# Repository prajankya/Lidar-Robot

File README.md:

## Unmanned Mapping Vehicle Using L.O.A.M. in Real-time
 L.O.A.M. - Lidar Odometry and Mapping in Real-time

This project is about an Unmanned Mobile Robot using L.O.A.M. (Lidar, Odometry And Mapping) in Real-time.

## Abstract
The robot uses a Laser distance sensor(Lidar) which gives distance to the first obstacle in its line-of-sight and the sensor. Making this sensor rotate gives us distance of all the obstacles from the sensor, which in fact is the map of the surrounding. This sensor, with other sensors like odometry and IMU(Inertial measurement Unit), mounted on a mobile moving base and complex algorithms driving the robot autonomously help make a to-scale map of the surrounding.

## Basic contruction
The Bot uses ROS(Robot Operating System) at its core running on a compact mobile CPU. It uses IMU(Inertial measurement Unit) for its orientation feedback. The base comprise of a square frame with four omni wheel on its corners driven by high torque BLDC motors. The Bot works on 24v DC and have internal power distribution and conversion unit. The bot first takes in the lidar input, and process that into a map fusing together with  odometry input and IMU input. The Odometry sensor is a “Castor Feedback sensor” which consist of two rotary encoders, one reading the angle or rotation, and other the length in that direction. This type of feedback can be universally used for any type of terrain robots with very good accuracy. This bot can be controlled from a remote computer, on which we can even see the 3D Model and see the model within the map in Real time. The GUI remote can be used to save the map or load the map in the system. Taking all the properties in consideration,  Lidar Robot with L.O.A.M. is a very robust platform with variety of robotics applications.

## How to Install
rosdep install --from-paths /opt/ros/jade --ignore-src

rosdep install --from-paths Lidar-Robot/src --ignore-src

6th sem, 2017 Batch  
Department of Automation and Robotics.  
B. V. Bhoomaraddi College of Engineering and Technology, Hubli

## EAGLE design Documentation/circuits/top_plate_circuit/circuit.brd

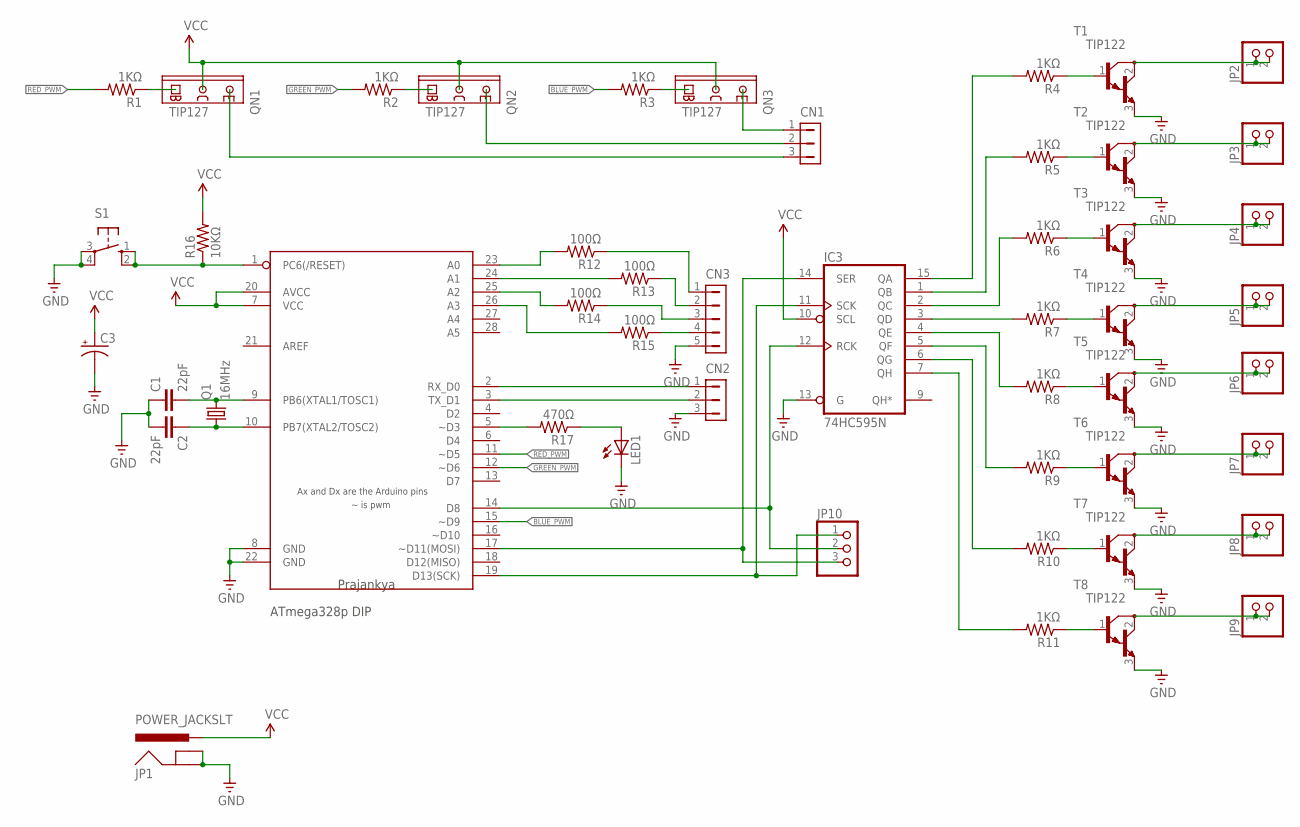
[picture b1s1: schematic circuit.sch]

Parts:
C1, C2: 22pF; C025-025X050
C3: CPOL-USTT2D6L; TT2D6L
CN1, CN2: HDR-1X3-70543-?; 70543-03
CN3: HDR-1X5-70543-?; 70543-05
IC3: 74HC595N; DIL16
JP1: POWER_JACKSLT; POWER_JACK_SLOT
JP2, JP3, JP4, JP5, JP6, JP7, JP8, JP9: PINHD-1X2; 1X02
JP10: PINHD-1X3; 1X03
LED1: LED5MM
Q1: 16MHz; HC49U-V
QN1, QN2, QN3: TIP127; TO220AV
R1, R2, R3, R4, R5, R6, R7, R8, R9, R10, R11: 1KΩ; AXIAL-0.4
R12, R13, R14, R15: 100Ω; AXIAL-0.4
R16: 10KΩ; 0207/10
R17: 470Ω; 0207/12
S1: 10-XX; B3F-10XX
T1, T2, T3, T4, T5, T6, T7, T8: TIP122; TO220
U$1: ATMEGA328P_DIP; ATMEGA328_CUSTOMPAD

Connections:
BLUE_PWM: R3.P$2 (2), U$1.15 (~D9)
GND: C1.1, C2.2, C3.-, CN2.3, CN3.5, IC3.8 (GND), IC3.13 (G), JP1.GND@1 (GNDBREAK), JP1.GND@2 (GND), LED1.K (C), S1.3, S1.4 (P1), T1.3 (E), T2.3 (E), T3.3 (E), T4.3 (E), T5.3 (E), T6.3 (E), T7.3 (E), T8.3 (E), U$1.8 (GND), U$1.22 (GND)
GREEN_PWM: R2.P$2 (2), U$1.12 (~D6)
N1: JP2.1, JP2.2, T1.2 (C)
N2: JP3.1, JP3.2, T2.2 (C)
N3: JP4.1, JP4.2, T3.2 (C)
N4: JP5.1, JP5.2, T4.2 (C)
N5: JP6.1, JP6.2, T5.2 (C)
N6: JP7.1, JP7.2, T6.2 (C)
N7: JP8.1, JP8.2, T7.2 (C)
N8: JP9.1, JP9.2, T8.2 (C)
unnamed: CN1.3, QN1.E
unnamed: CN1.2, QN2.E
unnamed: CN1.1, QN3.E
unnamed: QN1.B, R1.P$1 (1)
unnamed: QN2.B, R2.P$1 (1)
unnamed: QN3.B, R3.P$1 (1)
unnamed: R4.P$1 (1), T1.1 (B)
unnamed: R5.P$1 (1), T2.1 (B)
unnamed: R12.P$2 (2), U$1.23 (A0)
unnamed: IC3.15 (QA), R4.P$2 (2)
unnamed: R13.P$2 (2), U$1.24 (A1)
unnamed: IC3.1 (QB), R5.P$2 (2)
unnamed: R6.P$1 (1), T3.1 (B)
unnamed: R14.P$2 (2), U$1.25 (A2)
unnamed: IC3.2 (QC), R6.P$2 (2)
unnamed: R7.P$1 (1), T4.1 (B)
unnamed: R15.P$2 (2), U$1.26 (A3)
unnamed: IC3.3 (QD), R7.P$2 (2)
unnamed: R8.P$1 (1), T5.1 (B)
unnamed: CN2.1, U$1.2 (RX_D0)
unnamed: IC3.4 (QE), R8.P$2 (2)
unnamed: R9.P$1 (1), T6.1 (B)
unnamed: CN2.2, U$1.3 (TX_D1)
unnamed: IC3.5 (QF), R9.P$2 (2)
unnamed: R10.P$1 (1), T7.1 (B)
unnamed: R17.2, U$1.5 (~D3)
unnamed: IC3.6 (QG), R10.P$2 (2)
unnamed: R11.P$1 (1), T8.1 (B)
unnamed: LED1.A, R17.1
unnamed: IC3.7 (QH), R11.P$2 (2)
unnamed: IC3.11 (SCK), JP10.1, U$1.19 (D13(SCK))
unnamed: IC3.12 (RCK), JP10.2, U$1.14 (D8)
unnamed: C2.1, Q1.1, U$1.10 (PB7(XTAL2/TOSC2))
unnamed: C1.2, Q1.2, U$1.9 (PB6(XTAL1/TOSC1))
unnamed: CN3.1, R12.P$1 (1)
unnamed: CN3.2, R13.P$1 (1)
unnamed: CN3.3, R14.P$1 (1)
unnamed: CN3.4, R15.P$1 (1)
unnamed: IC3.14 (SER), JP10.3, U$1.17 (~D11(MOSI))
unnamed: R16.1, S1.1 (S), S1.2 (S1), U$1.1 (PC6(/RESET))
RED_PWM: R1.P$2 (2), U$1.11 (~D5)
VCC: C3.+, IC3.10 (SCL), IC3.16 (VCC), JP1.PWR, QN1.C, QN2.C, QN3.C, R16.2, U$1.7 (VCC), U$1.20 (AVCC)

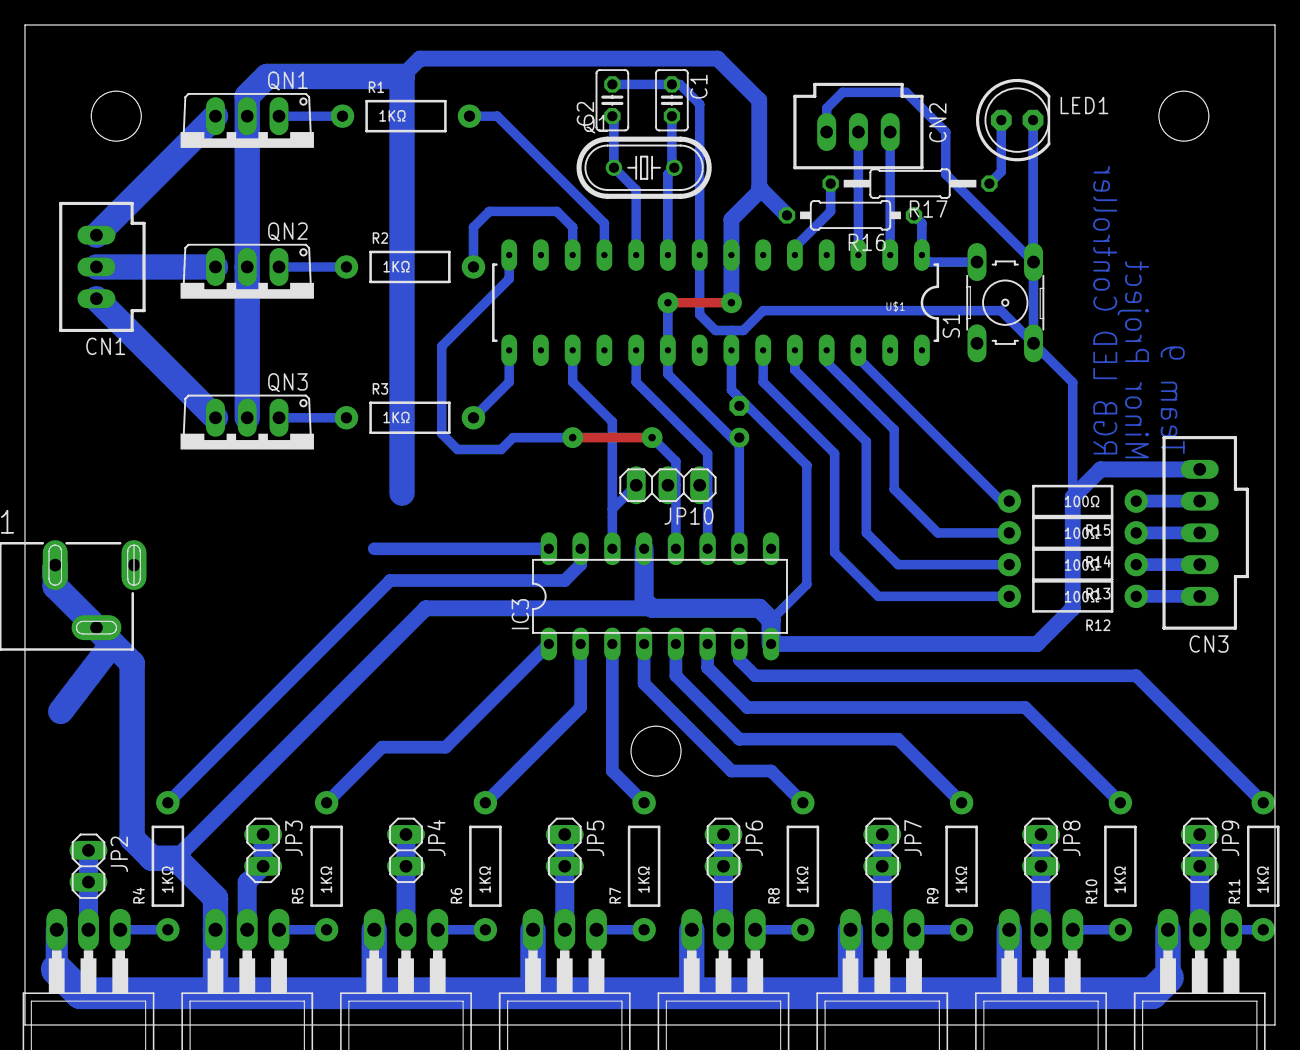
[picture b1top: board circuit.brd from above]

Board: 2 copper layers, 100.0 x 80.0 mm, 49 parts (1 on the bottom side), 53 nets.

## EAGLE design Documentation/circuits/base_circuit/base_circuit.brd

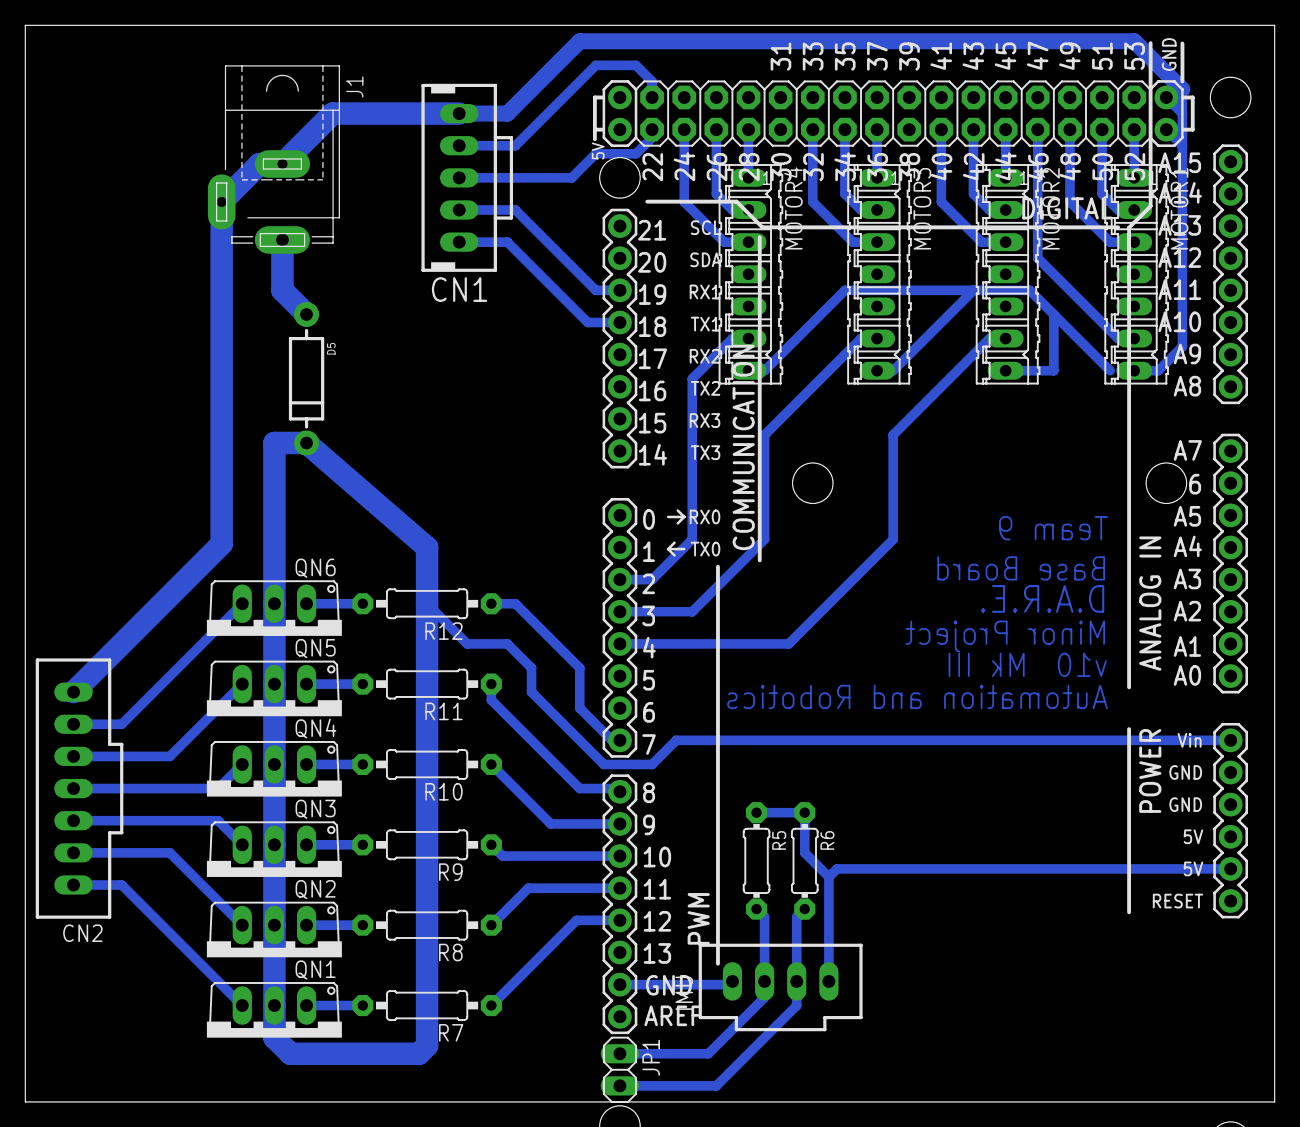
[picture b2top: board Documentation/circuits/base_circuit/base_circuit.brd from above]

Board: 2 copper layers, 98.7 x 85.1 mm, 25 parts (0 on the bottom side), 44 nets.

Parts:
CN1: MTE-100-5VL
CN2: 70543-07
D5: DIODE-1N4001
IMU: 70543-04
J1: SPC4078
JP1: 1X02
MOTOR1: m1; 07P
MOTOR2: m2; 07P
MOTOR3: m3; 07P
MOTOR4: m4; 07P
QN1, QN2, QN3, QN4, QN5, QN6: TIP127; TO220AV
R5, R6: 2.2k; 0204/7
R7, R8, R9, R10, R11, R12: 0207/10
U1: ARDUINO-MEGAFULL; ARDUINO_MEGA

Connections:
BRAKE-M1: MOTOR1.1, U1.52
BRAKE-M2: MOTOR2.1, U1.44
BRAKE-M3: MOTOR3.1, U1.36
BRAKE-M4: MOTOR4.1, U1.28
DIR-M1: MOTOR1.3, U1.48
DIR-M2: MOTOR2.3, U1.40
DIR-M3: MOTOR3.3, U1.32
DIR-M4: MOTOR4.3, U1.24
DIS-M1: MOTOR1.2, U1.50
DIS-M2: MOTOR2.2, U1.42
DIS-M3: MOTOR3.2, U1.34
DIS-M4: MOTOR4.2, U1.26
FEEDBACK_IN1: CN1.3, U1.22
FEEDBACK_IN2: CN1.4, U1.23
FEEDBACK_INT1: CN1.1, U1.18
FEEDBACK_INT2: CN1.2, U1.19
GND: CN1.5, CN2.7, IMU.1, J1.1, J1.2, MOTOR1.7, MOTOR2.7, MOTOR3.7, MOTOR4.7, U1.GND@2, U1.GND@3, U1.GND@4
L1: R7.1, U1.12
L2: R8.1, U1.11
L3: R9.1, U1.10
L4: R10.1, U1.9
L5: R11.1, U1.8
L6: R12.1, U1.7
unnamed: QN1.B, R7.2
unnamed: QN2.B, R8.2
unnamed: QN3.B, R9.2
unnamed: QN4.B, R10.2
unnamed: QN5.B, R11.2
unnamed: QN6.B, R12.2
unnamed: D5.A, J1.3
unnamed: CN2.1, QN1.E
unnamed: CN2.2, QN2.E
unnamed: CN2.3, QN3.E
unnamed: CN2.4, QN4.E
unnamed: CN2.5, QN5.E
unnamed: CN2.6, QN6.E
SCL: IMU.3, JP1.2, R6.2
SDA: IMU.2, JP1.1, R5.2
SPEED-M1: MOTOR1.6, U1.46
SPEED-M2: MOTOR2.6, U1.4
SPEED-M3: MOTOR3.6, U1.3
SPEED-M4: MOTOR4.6, U1.2
VCC: IMU.4, R5.1, R6.1, U1.3.3V
VCC/2: D5.C, QN1.C, QN2.C, QN3.C, QN4.C, QN5.C, QN6.C, U1.VIN

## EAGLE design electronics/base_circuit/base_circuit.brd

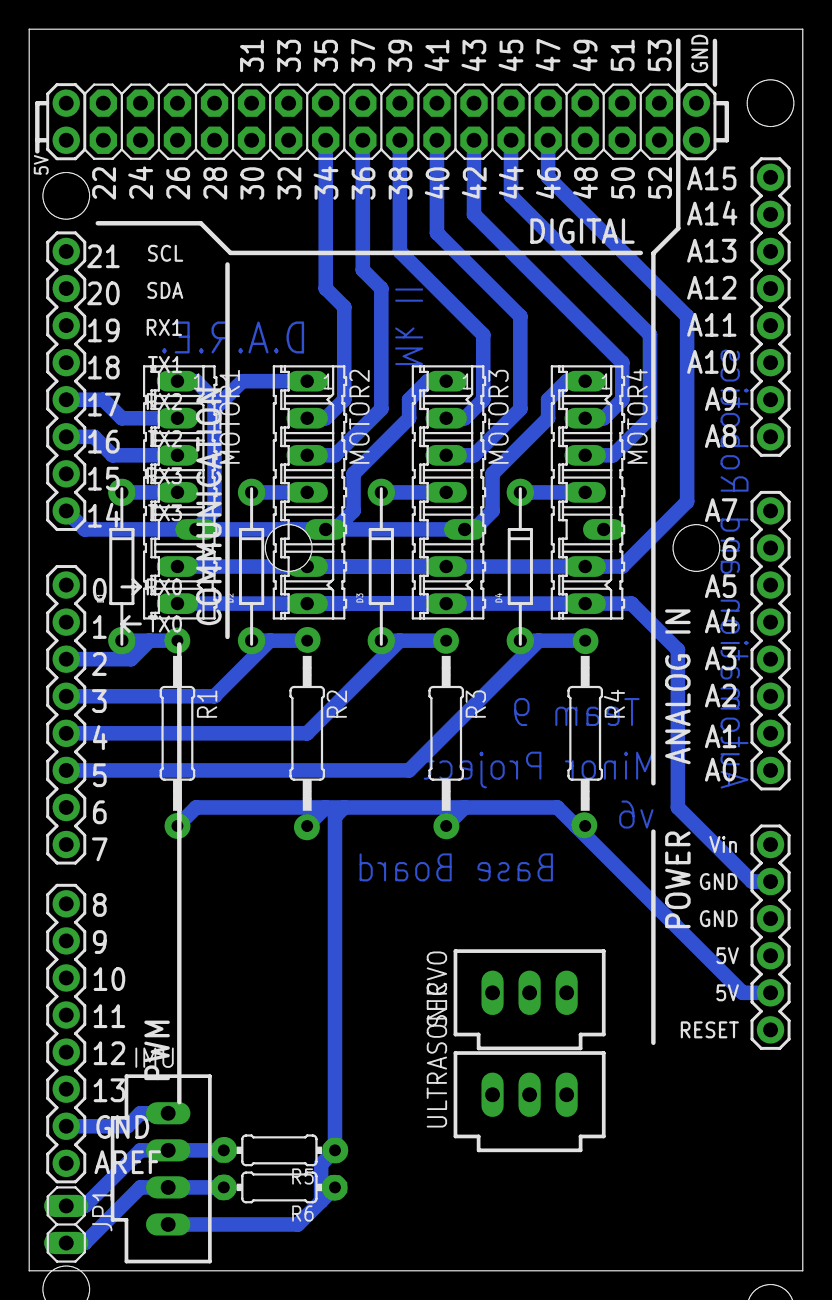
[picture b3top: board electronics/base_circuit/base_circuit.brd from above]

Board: 2 copper layers, 53.0 x 85.1 mm, 19 parts (0 on the bottom side), 23 nets.

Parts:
D1, D2, D3, D4: DIODE-1N4148
IMU: 70543-04
JP1: 1X02
MOTOR1: m1; 07P
MOTOR2: m2; 07P
MOTOR3: m3; 07P
MOTOR4: m4; 07P
R1, R2, R3, R4: 4.7k; 0207/12
R5, R6: 2.2k; 0204/7
SERVO: 70543-03
U1: ARDUINO-MEGAFULL; ARDUINO_MEGA
ULTRASONIC: 70543-03

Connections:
BRAKEPIN: MOTOR1.1, MOTOR2.1, MOTOR3.1, MOTOR4.1, U1.14
DIR-M1: MOTOR1.3, U1.16
DIR-M2: MOTOR2.3, U1.36
DIR-M3: MOTOR3.3, U1.40
DIR-M4: MOTOR4.3, U1.44
DIS-M1: MOTOR1.2, U1.17
DIS-M2: MOTOR2.2, U1.34
DIS-M3: MOTOR3.2, U1.38
DIS-M4: MOTOR4.2, U1.42
GND: IMU.1, MOTOR1.7, MOTOR2.7, MOTOR3.7, MOTOR4.7, SERVO.3, U1.GND@0, U1.GND@1, U1.GND@4
unnamed: D1.C, MOTOR1.4
unnamed: D2.C, MOTOR2.4
unnamed: D3.C, MOTOR3.4
unnamed: D4.C, MOTOR4.4
SCL: IMU.3, JP1.2, R6.2
SDA: IMU.2, JP1.1, R5.2
SPEEDPIN: MOTOR1.6, MOTOR2.6, MOTOR3.6, MOTOR4.6, U1.46
TACHO-M1: D1.A, R1.1, U1.2
TACHO-M2: D2.A, R2.1, U1.3
TACHO-M3: D3.A, R3.1, U1.4
TACHO-M4: D4.A, R4.1, U1.5
VCC: IMU.4, R1.2, R2.2, R3.2, R4.2, R5.1, R6.1, U1.3.3V
VCC/2: SERVO.2, U1.VIN

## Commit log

2016-04-02 Added Submodules
2016-04-02 Create gh-pages branch via GitHub
2016-04-02 Updateed Readme.md with author
2016-04-03 Added Datasheets in the Documentation
2016-04-03 v1 of Base circuit
2016-04-03 v1 of base program
2016-04-03 v2 of base program
2016-04-03 Initial Programs
2016-04-03 deleted electronics as it is added in the individual repo of base
2016-04-04 Removed Electronics and Programming folders as they are going in the Dedicated repositories
2016-04-04 removed download buttons
2016-04-04 solved scratch compiling closed #1
2016-04-04 updated readme with darshan link
2016-04-04 updated readme with typo @Belavatagi
2016-04-04 added link to @pujarmani
2016-04-04 Added readme
2016-04-05 Working towards #4 , added led pins
2016-04-05 Added circuits folder closed #6
2016-04-06 updated Circuit
2016-04-06 changed the whole circuit to use speed control for individula motors and also added connections for top plate design leds
2016-04-06 added master start
2016-04-08 edited BRD file
2016-04-08 Base is receiving standard message instead of custom message
2016-04-08 Edited the base program to take new speed and brake control
2016-04-09 added top plate design program functions closed #15
2016-04-09 added led functions
2016-04-09 added outIn LED function
2016-04-16 Updated Odometry output
2016-04-16 verified odom is working
2016-04-21 Added Design Service closed #16 , changed IMU use to a separate cpp, making it optional with one declare closed #19
2016-04-21 Configurable firmware
2016-04-29 Verified the problem with led design
2016-04-30 Updated URDF tf_broadcaster
2016-04-30 Adding v2 Models
2016-04-30 testing with base speed pwm problem
2016-04-30 Repaired Speed Problem, closed #24
2016-04-30 Repaired Different motor speed Problem, closed #24
2016-05-01 Repaired speed problem of motors
2016-05-02 Added magnetometer heading in between
2016-05-02 Expected working odom
2016-05-02 added Hector mapping
2016-05-27 Added Abstract to readme
2016-05-27 Added Zenodo DOI
2016-05-27 Added rendered images in CAD Models
2016-05-27 Added Documentation report and project proposal
2016-05-27 added Gui v1 design in Documentation
2016-05-27 Added Datasheet manual of RPLidar
2016-05-27 Updated Submodules to latest commits
2016-05-28 Shifted to custom website
2016-05-30 step 1 with three js
2016-06-03 Added hover
2016-06-03 added tween.js
2016-06-03 added tween.js edited original models
2016-06-05 Optimized Models with meshmixer
2016-06-05 Meshes loaded successfully, but raycaster not working individually
2016-06-14 Removed Submodules
    Updated and Unified the base code removing all the submodules
2016-06-14 Removed Gitmodules
2016-06-14 Added gitignore for devel and build folders of catkin make
2016-06-14 Added node webserver
2016-06-14 removed node modules
2016-06-14 Added node_modules in gitignore
2016-06-14 removed src
2016-06-14 Moved to src
2016-06-14 Made Server.launch file
2016-06-14 added Meshes
2016-06-14 node Server is Working
2016-06-14 Added ROS control center, Repaired the dependancy on port for index.html
2016-06-14 Added Base and tf nodes
2016-06-15 Added local javascript files, moved webserver files to a subfolder, edited server.launch added dependencies in package.xml
2016-06-15 Added Compressed files
2016-06-15 Removed control center
2016-06-15 added ROS Control Center
2016-06-15 Added how to install step in README.md
2016-06-15 Updated Solidworks Models v3
2016-06-15 Tiding the repo
2016-06-15 Moved circuits to Documentation
2016-06-15 Added STL and PLY models in CAD
2016-06-15 updates to RPlidar
2016-06-15 Moved Models in the ros package for xacro discovery
2016-06-15 Base model Down scaled
2016-06-15 further scaled down to 0.01x
2016-06-15 further scaled down to 0.001x
2016-06-15 Scaled back up the base
2016-06-15 added c clamp and shaft to the xacro
2016-06-15 Added dae of wheel and removed unrequired files
2016-06-15 setting wheel
2016-06-15 Added wheel collada with texture
2016-06-15 updating robot.xacro
2016-06-15 updating robot.xacro second wheel
2016-06-16 Updated Readme to How to install for system dependencies
2016-06-16 Added Top Plate to URDF
2016-06-16 Added circuit plate
2016-06-16 Updated server.js for spawn, printing stdout and stderr now
2016-06-16 Updated to run server seemlessly without warning of xacro
2016-06-16 Changed distance from center Changed distance from center of c clamp motor shaft and wheel to a variable
2016-06-16 Added Feedback and Studs for it
2016-06-16 Added RPlidar base in model
2016-06-16 Added RPlidar Bottom
2016-06-16 Added Lidar UP updated stud.stl with proper binary encoding
2016-06-16 Updated RVIZ
    Files working with tf jointstatepublisher and robot_tf_publisher perfectly on rviz as well as website
2016-06-16 Added keyboardteleop feature
2016-06-17 Removed host name dependency of ros-mini
2016-06-17 Cleaned a lot
2016-06-17 Added Gazebo
2016-06-17 Moved rviz to extras
2016-06-17 Updated URDF with Gazebo wheels
2016-06-17 Gazebo is functioning
2016-06-18 Added ROS-Control
    Partially added, gazebo model does not place shaft correctly yet.
2016-06-18 Added git ignore
2016-06-18 Removed Controller setup
    Removed controller as the real bot does not have any feedback on wheels, so cannot use the PID control, though gazebo provides it.
2016-06-18 Working Gazebo and rviz with movement from web UI
2016-06-18 Cleaning GH branch
2016-06-18 added three.js in javascripts
2016-06-18 Removed node modules folder
2016-06-18 Added node_modules exception in gitignore
2016-06-18 Removed optimized
2016-06-18 Made gazebo empty launch
2016-06-18 Updated meshs json with all except wheel
2016-06-18 Added motor and c clamp to model
2016-06-18 Cleaned models dir
2016-06-19 Cleaned repo, Hector SLAM not working
2016-06-19 Removed Hector slam
2016-06-19 Added connection status in web UI
2016-06-19 Move base working with 2D goal
2016-06-19 Removed Husky, unrequired folder
2016-06-20 Added Move Base, 2D Nav goals working
2016-06-27 Added frontier_exploration
2016-06-27 solving frontier git connection problem
2016-06-27 Added frontier exploration
2016-06-28 Added Auto Explorer
2016-06-28 Solved build dependancy with frontier_exploration
2016-06-28 Exploration working Cleaned repo, Auto exit node server on client close
2016-06-28 Partial commit with map on web not working so commented out
2016-06-28 Separated Core and gsim, rviz
2016-07-03 Added Create AP Package
2016-07-03 Added Create Ap to node automated the creating AP process by adding it to the default server.js
2016-07-03 Made first Page for control by mobile also added dependencies in package.xml
2016-07-03 Added Port forwarder to 80 removed all the dependancies and kept direct password in sudo and also forwarded 80 to 8080
2016-07-03 Web Console is working Added listener to rosout_agg from web to show the console output
2016-07-04 Added controller Connected start Mapping as a service to the Web UI button
2016-07-04 Added some material colors in gh-pages
2016-07-04 Changed the server address
2016-07-04 Solving Costmap timeout
2016-07-04 Solved the costmap timeout problem
    first need to run lidar_robot.launch
    then gazebo.launch
    and then at last run move_base.launch
2016-07-04 Added Gazedbo sim in main launch to remove the time inconsistancy problem
2016-07-05 Basic v1
2016-07-05 Removed Accelerometer dependancy Using only Magnetometer in the string
2016-07-05 Cleaned, Added base.cpp
2016-07-05 Solved typo in launch file
2016-07-05 temp_save
2016-07-06 Moved index file inside solved auto IP closed #23 solved password problem in sudo module
2016-07-06 Moved IMU code to firmware.cpp
2016-07-06 Moved IMU code to firmware.cpp Un Commented create AP and ROSlaunch in serverjs
2016-07-06 Everything connected
2016-07-06 Added 3d.html in link
2016-07-06 Adding slider
2016-07-06 Added Speed slider
2016-07-06 All connected, just to update odom->base_link
2016-07-06 Solved issue with RPlidar Frame
2016-07-06 Added ROS_bags
2016-07-07 Working Odom Yet to verify,also add the imu_yaw
2016-07-07 Trying to solve #15
2016-07-07 Solved the compilation error
2016-07-07 Upadated RPlidar fro mgit source
2016-07-07 Solved the linking of gmapping Odom topic name was not same
2016-07-07 Odometry working, but not correctly Need to reset everything with reference frame Need to calibrate TF of IMU to base
2016-07-07 closed #15 #29 and #27
2016-07-07 Updated xacro with proper frames
2016-07-07 IMu rotation not working
    Change the placement of IMU to the center and then remove all the transformations for imu to baselink
2016-07-09 Possibly adding the Imu In center
2016-07-11 Starting with Hector Slam
2016-07-11 Added mapping default
2016-07-11 Hector mapping is working
2016-07-11 Adding localization
2016-07-11 Added hector navigation
2016-07-11 Updated package.xml
2016-07-11 Added hector exploration node problem with costmap timeout
2016-07-11 Added move_base
2016-07-11 Cleaning and many other changes
2016-07-11 Updating base_controller
2016-07-11 Base_controller done
2016-07-11 Base Controller working
2016-07-11 Working,But HUGE PROBLEM Base is moving with unknown speed and hence is not safe to work with all the different motors show different speeds
2016-08-09 Conducting Reseach under REU
2016-08-09 Added basic references

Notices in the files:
README.md:
GPL Licence
parts and their libraries:
con-hdrs40: Copyright (C) 2004, Bob Starr (bobstarr@mindspring.com)
SparkFun-Boards: Licensing: Creative Commons ShareAlike 4.0 International - https://creativecommons.org/licenses/by-sa/4.0
supply0: Copyright (C) 2007, Bob Starr
